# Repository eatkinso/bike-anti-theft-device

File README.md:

# Bike Anti-Theft Device

A portable, concealed device to prevent bike theft and facilitate tracking, centered around the STM32WLCC integrated microcontroller and SubGHz transceiver. This project was created for [ECE445 Spring 2022 at the University of Illinois at Urbana-Champaign](https://courses.physics.illinois.edu/ece445/projects.asp). 

# Development Folder Structure

- *Documentation*: Proposal, design document, final paper, and presentation for ECE 445. 
- *References*: Selected datasheets and reference manuals. 
- *Notebooks*: Lab notebooks during the development process. 
- *Hardware*: KiCAD schematic and layout files for each board used in the project. 
- *Firmware*: Microcontroller code for the STM32WLCC used in our project. Note that the final demo code is in SingleCore_UART -- the other folders contain various debugging firmware projects since it is easier to keep track of things during the development process by re-initializing a project in CubeMX for different tests rather than continuously using the same project. 

# Lab Notebook Structure

- Each group member will write entries in their markdown notebook to describe the development and debugging process. 
- Daily notebook entries must have a descriptive title, date, and the user's name. 
- Notebook entries referring to specific features, etc should identify the feature by its commit hash. For readability it may be better to embed images (of schematics, test setups, hand sketches etc) in the markdown notebook itself depending on the context.
- Lab notebook entries will not be removed or modified once written down. 
- Lab data, code to generate plots, etc is in a different folder since it is shared. Always save the original data for all trials, even if you only end up using some of the data for the analysis. 

# Workflow notes 
- VScode is convenient to write and render markdown. 
- TEXstudio is convenient to write and render LaTEX documents for reports, etc. Always save the .tex source to git, not the generated PDF. 
- Always commit the ENTIRE kicad project directory for PCBs. This prevents issues with footprint and symbol libraries 
since the entire project directory includes the backup and symbol rescue files.
- STM32CubeMX is used to generate peripheral initialization code and makefiles. We used an STLINK-V3 with [Black Magic Probe](https://github.com/blackmagic-debug/blackmagic) firmware running in PC-hosted mode for debugging.

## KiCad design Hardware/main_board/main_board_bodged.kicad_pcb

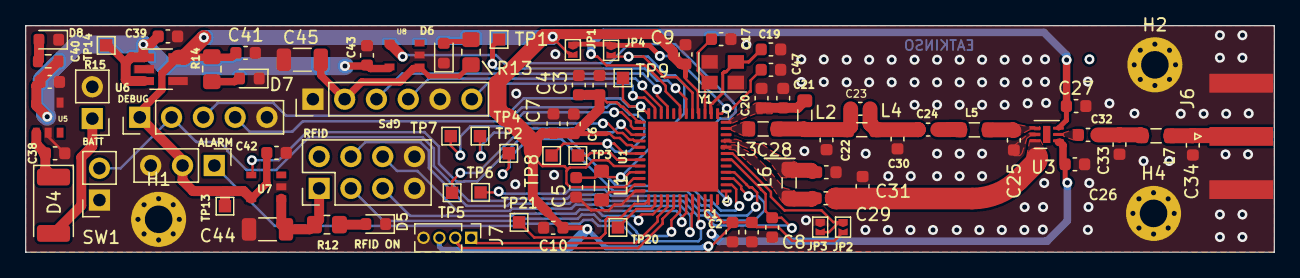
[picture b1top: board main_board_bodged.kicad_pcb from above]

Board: 2 copper layers, 99.8 x 18.1 mm, 87 parts (0 on the bottom side), 55 nets.

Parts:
C1, C3, C9, C10: 4.7u; C_0603_1608Metric
C2, C4: 100n; C_0603_1608Metric
C5: 470n; C_0603_1608Metric
C6, C38, C39, C40, C41, C42, C43, C47: 1u; C_0603_1608Metric
C7: 10n; C_0603_1608Metric
C8: 0.1u; C_0603_1608Metric
C17, C19: 22p; C_0603_1608Metric
C20: 47n; C_0603_1608Metric
C21, C24: 68p; C_0603_1608Metric
C22: 0.7p; C_0603_1608Metric
C23: 2p; C_0603_1608Metric
C25: DNP; C_0603_1608Metric
C26, C27: 1000p; C_0603_1608Metric
C28: 4.7p; C_0603_1608Metric
C29: 3p; C_0603_1608Metric
C30: 5.1p; C_0603_1608Metric
C31: 1p; C_0603_1608Metric
C32: 56p; C_0603_1608Metric
C33, C34: 3.3p; C_0603_1608Metric
C44, C45: 10u; C_1206_3216Metric
D4: D; D_2010_5025Metric
D5, D6, D7, D8: LED; LED_0603_1608Metric
H1, H2, H4: MountingHole_Pad; MountingHole_2.2mm_M2_Pad_Via
J1: ALARM; PinHeader_1x03_P2.54mm_Vertical
J2: RFID_CONN; PinHeader_2x04_P2.54mm_Vertical
J3: GPS_CONN; PinHeader_1x06_P2.54mm_Vertical
J5: DEBUG; PinHeader_1x05_P2.54mm_Vertical
J6: ANTENNA2; SMA_Amphenol_132289_EdgeMount
J7: Conn_01x04_Male; PinHeader_1x04_P1.27mm_Vertical
J8: BATT; PinHeader_1x02_P2.54mm_Vertical
JP1: SolderJumper_2_Bridged; tinyjumper
JP2, JP3, JP4: SolderJumper_2_Open; tinyjumper
L1: 15u; L_0805_2012Metric_Pad1.05x1.20mm_HandSolder
L2: 47n; L_0805_2012Metric_Pad1.05x1.20mm_HandSolder
L3: 4.45n; L_0805_2012Metric_Pad1.05x1.20mm_HandSolder
L4: 3.6n; L_0805_2012Metric_Pad1.05x1.20mm_HandSolder
L5: 8.7n; L_0805_2012Metric_Pad1.05x1.20mm_HandSolder
L6: 11n; L_0805_2012Metric_Pad1.05x1.20mm_HandSolder
L7: 9.1n; L_0805_2012Metric_Pad1.05x1.20mm_HandSolder
R12, R13, R14: 200R; R_0805_2012Metric_Pad1.20x1.40mm_HandSolder
R15: 200R; R_0603_1608Metric
SW1: SW_Push; PinSocket_1x02_P2.54mm_Vertical
TP1, TP2, TP3, TP4, TP5, TP6, TP7, TP8, TP9, TP13, TP14, TP20, TP21: TestPoint; TestPoint_Pad_1.0x1.0mm
U1: STM32WL55_UFQFPN48; QFN-48-1EP_7x7mm_P0.5mm_EP5.6x5.6mm
U3: SKY13370-374LF; DFN-6-1EP_2x2mm_P0.5mm_EP0.6x1.37mm
U5: AP7370-50W5-7; SOT25
U6: S-1135A33-M5T1U; SOT-23-5_HandSoldering
U7, U8: AP22811BW5-7; SOT25
Y1: Crystal_GND24; Oscillator_SMD_Abracon_ASE-4Pin_3.2x2.5mm

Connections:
+3V3: C1.1, C2.1, C3.1, C4.1, C6.1, C7.1, C9.1, C10.1, C41.1, C42.1, J1.2, J5.1, J7.3, JP1.2 (B), JP2.2 (B), R14.1, TP13.1, U1.11 (VDD), U1.28 (VDDRF), U1.37 (VBAT), U1.41 (VDDA), U1.44 (VDD), U1.46 (VDDSMPS), U6.5 (VOUT), U7.5 (IN)
+3V3_RFID: C44.1, J2.1, R12.1, U7.1 (OUT)
+5V: C39.1, C40.1, C43.1, R15.2, TP14.1, U5.5 (VOUT), U6.1 (VIN), U6.3 (ON), U8.5 (IN)
+5V_GPS: C45.1, J3.2, R13.1, U8.1 (OUT)
DBUG_JTDO_SWO: TP21.1, U1.1 (PB3)
DEBUG_JTCK_SWCLK: J5.4, TP8.1, U1.42 (PA14)
DEBUG_JTDI: TP3.1, U1.43 (PA15)
DEBUG_JTMS_SWDIO: J5.3, TP9.1, U1.36 (PA13)
DEBUG_JTRST: TP20.1, U1.2 (PB4)
GND: C1.2, C2.2, C3.2, C4.2, C5.2, C6.2, C7.2, C8.2, C9.2, C10.2, C17.1, C19.1, C20.2, C21.2, C22.2, C25.2, C26.1, C27.2, C28.2, C30.2, C31.1, C33.2, C34.2, C38.2, C39.2, C40.2, C41.2, C42.2, C43.2, C44.2, C45.2, C47.2, D5.1 (K), D6.1 (K), D7.1 (K), D8.1 (K), H1.1, H2.1, H4.1, J1.3, J2.7, J2.8, J3.1, J3.5, J5.5, J6.2 (Ext), J7.4, J8.2, JP3.1 (A), SW1.1, U1.48 (VSSSMPS), U3.5 (GND), U5.2 (GND), U5.4 (NC), U6.2 (VSS), U6.4 (NC), U7.2 (GND), U8.2 (GND), Y1.2, Y1.4
GPS_~PWR: U1.13 (PA5), U8.4 (~EN)
LPUART1_NRX: C26.2, U1.10 (PA3), U3.1 (VC1)
LPUART1_NTX: J1.1, U1.9 (PA2)
NRST: C8.1, J5.2, SW1.2, U1.18 (NRST)
unnamed: C5.1, JP4.2 (B), L1.1, U1.29 (VDDRF1V55), U1.45 (VFBSMPS)
unnamed: C17.2, U1.27 (OSC_OUT), Y1.1
unnamed: C19.2, U1.26 (OSC_IN), Y1.3
unnamed: C20.1, C21.1, L2.1, U1.24 (VR_PA)
unnamed: C22.1, C23.1, L2.2, L3.2, L4.1
unnamed: C23.2, C24.1, C30.1, L4.2
unnamed: C24.2, L5.1
unnamed: C25.1, L5.2, U3.4 (RF2)
unnamed: C28.1, L6.1, U1.21 (RFI_N)
unnamed: C29.1, L6.2, U1.20 (RFI_P)
unnamed: C29.2, C31.2, U3.6 (RF1)
unnamed: C32.1, U3.2 (RFC)
unnamed: C32.2, C33.1, L7.1
unnamed: C34.1, J6.1 (In), L7.2
unnamed: C38.1, D4.1 (K), U5.1 (VIN)
unnamed: C47.1, JP1.1 (A), JP4.1 (A), U1.25 (VDDPA)
unnamed: D4.2 (A), J8.1
unnamed: D5.2 (A), R12.2
unnamed: D6.2 (A), R13.2
unnamed: D7.2 (A), R14.2
unnamed: D8.2 (A), R15.1
unnamed: JP2.1 (A), JP3.2 (B), U1.19 (PH3-BOOT0)
unnamed: L1.2, U1.47 (VLXSMPS)
unnamed: L3.1, U1.23 (RFO_HP)
unnamed: TP1.1, U1.30 (PB0-VDD_TXCO)
unnamed: TP2.1, U1.16 (PA8)
unnamed: TP4.1, U1.40 (PC15-OSC32_OUT)
unnamed: TP5.1, U1.39 (PC14-OSC32_IN)
unnamed: TP6.1, U1.15 (PA7)
unnamed: TP7.1, U1.38 (PC13)
PA0: J2.6, U1.7 (PA0)
PA1: J2.4, U1.8 (PA1)
PA11: J3.4, U1.34 (PA11)
PA12: J3.6, U1.35 (PA12)
PB5: J2.5, U1.3 (PB5)
PB7: J7.2, U1.5 (PB7)
PB8: J2.3, U1.6 (PB8)
RFID_~PWR: U1.14 (PA6), U7.4 (~EN)
RFSW_VC2: C27.1, U1.31 (PB2), U3.3 (VC2)
USART1_RX: J3.3, U1.33 (PA10)
USART1_TX: J7.1, U1.4 (PB6)

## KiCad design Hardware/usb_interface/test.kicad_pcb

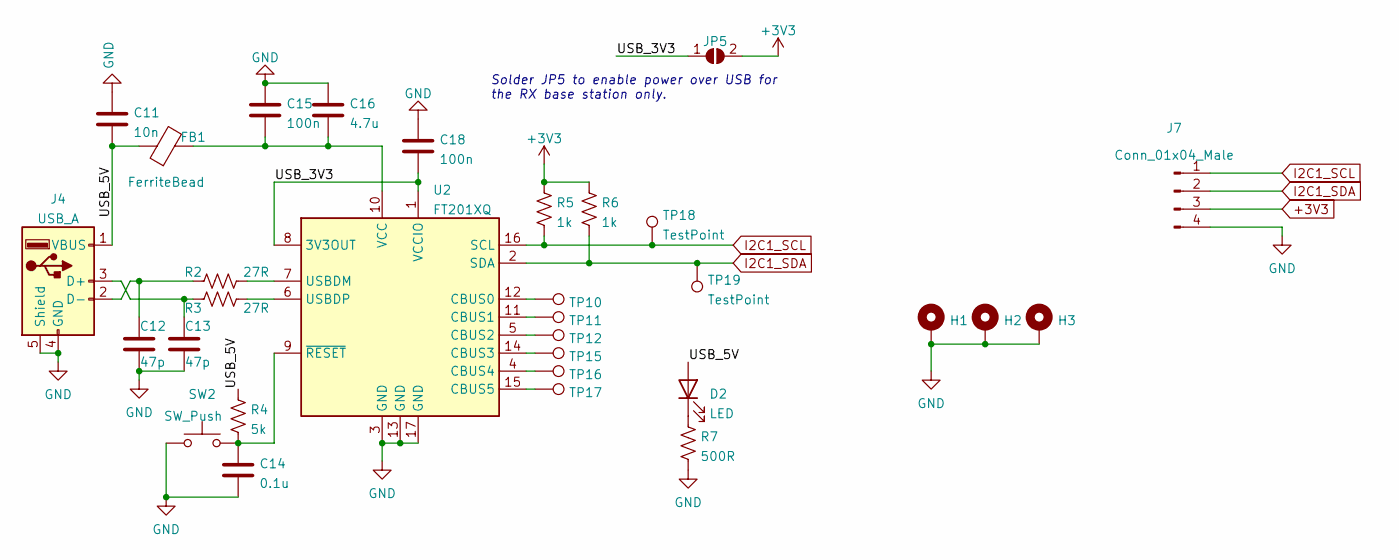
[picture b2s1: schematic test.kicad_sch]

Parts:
C11: 10n; C_0603_1608Metric
C12, C13: 47p; C_0603_1608Metric
C14: 0.1u; C_0603_1608Metric
C15, C18: 100n; C_0603_1608Metric
C16: 4.7u; C_0603_1608Metric
D2: LED; LED_0805_2012Metric
FB1: FerriteBead; LED_0805_2012Metric
H1, H2, H3: MountingHole_Pad; MountingHole_2.2mm_M2_Pad_Via
J4: USB_A; USB_A_Molex_67643_Horizontal
J7: Conn_01x04_Male; PinHeader_1x04_P1.27mm_Vertical
JP5: SolderJumper_2_Open; SolderJumper-2_P1.3mm_Open_RoundedPad1.0x1.5mm
R2, R3: 27R; R_0805_2012Metric_Pad1.20x1.40mm_HandSolder
R4: 5k; R_0805_2012Metric_Pad1.20x1.40mm_HandSolder
R5, R6: 1k; R_0805_2012Metric_Pad1.20x1.40mm_HandSolder
R7: 500R; R_0805_2012Metric_Pad1.20x1.40mm_HandSolder
SW2: SW_Push; PinSocket_1x02_P2.54mm_Vertical
TP10, TP11, TP12, TP15, TP16, TP17, TP18, TP19: TestPoint; TestPoint_Pad_1.0x1.0mm
U2: FT201XQ; QFN-16-1EP_4x4mm_P0.65mm_EP2.1x2.1mm

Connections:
+3V3: J7.3, JP5.2 (B), R5.1, R6.1
/USB_3V3: C18.2, JP5.1 (A), U2.1 (VCCIO), U2.8 (3V3OUT)
/USB_5V: C11.2, D2.2 (A), FB1.1, J4.1 (VBUS), R4.1
GND: C11.1, C12.2, C13.2, C14.2, C15.1, C16.1, C18.1, H1.1, H2.1, H3.1, J4.4 (GND), J4.5 (Shield), J7.4, R7.2, SW2.1, U2.3 (GND), U2.13 (GND), U2.17 (GND)
I2C1_SCL: J7.1, R5.2, TP18.1, U2.16 (SCL)
I2C1_SDA: J7.2, R6.2, TP19.1, U2.2 (SDA)
unnamed: C15.2, C16.2, FB1.2, U2.10 (VCC)
unnamed: C12.1, J4.2 (D-), R2.1
unnamed: C13.1, J4.3 (D+), R3.1
unnamed: D2.1 (K), R7.1
unnamed: TP16.1, U2.4 (CBUS4)
unnamed: TP12.1, U2.5 (CBUS2)
unnamed: R3.2, U2.6 (USBDP)
unnamed: R2.2, U2.7 (USBDM)
unnamed: C14.1, R4.2, SW2.2, U2.9 (~RESET)
unnamed: TP11.1, U2.11 (CBUS1)
unnamed: TP10.1, U2.12 (CBUS0)
unnamed: TP15.1, U2.14 (CBUS3)
unnamed: TP17.1, U2.15 (CBUS5)

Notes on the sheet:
Solder JP5 to enable power over USB for the RX base station only.

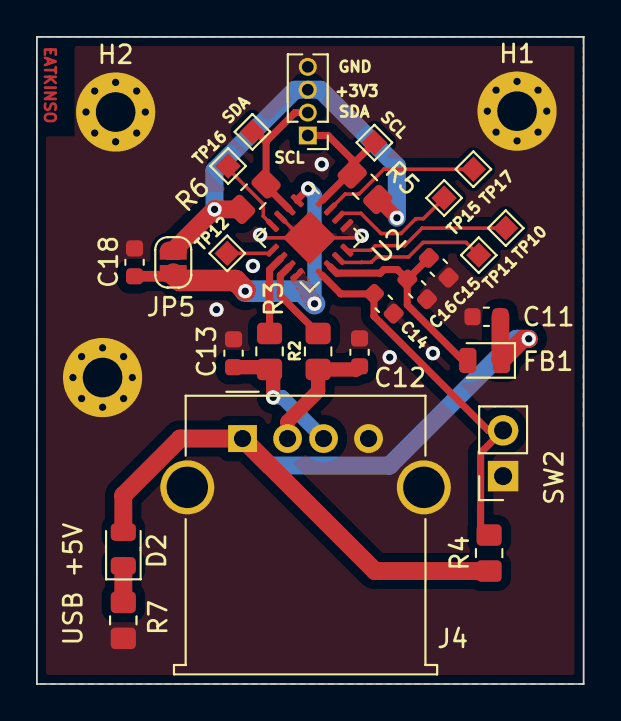
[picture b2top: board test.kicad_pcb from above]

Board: 2 copper layers, 30.4 x 35.9 mm, 31 parts (0 on the bottom side), 19 nets.

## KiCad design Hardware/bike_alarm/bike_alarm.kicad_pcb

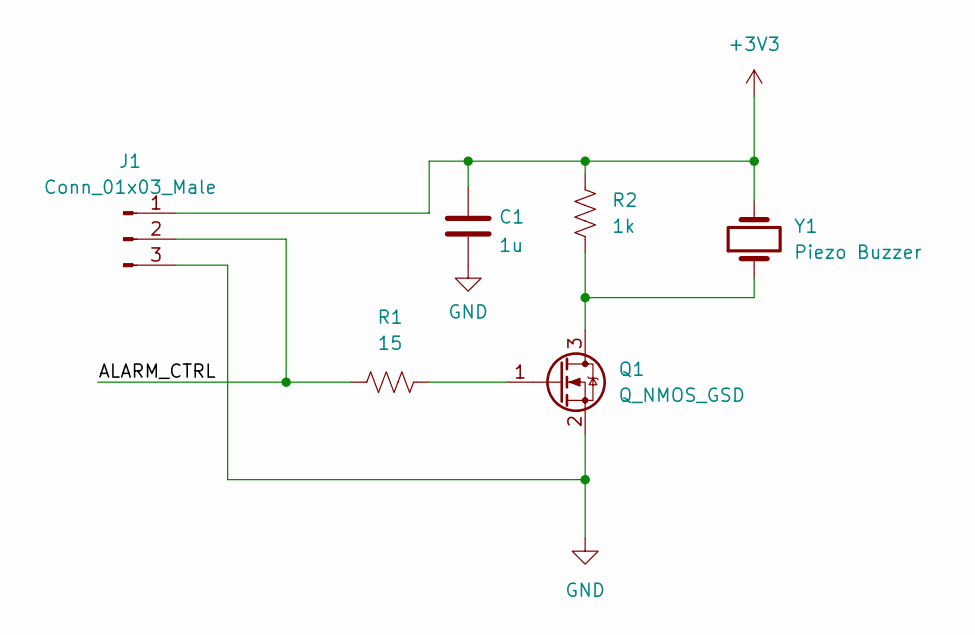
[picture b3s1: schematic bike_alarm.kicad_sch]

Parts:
C1: 1u; C_0805_2012Metric
J1: Conn_01x03_Male; PinHeader_1x03_P2.54mm_Vertical
Q1: Q_NMOS_GSD; SOT-23
R1: 15; R_0805_2012Metric_Pad1.20x1.40mm_HandSolder
R2: 1k; R_0805_2012Metric_Pad1.20x1.40mm_HandSolder
Y1: Piezo Buzzer; Crystal_AT310_D3.0mm_L10.0mm_Horizontal

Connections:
+3V3: C1.1, J1.1, R2.1, Y1.2
/ALARM_CTRL: J1.2, R1.1
GND: C1.2, J1.3, Q1.2 (S)
unnamed: Q1.1 (G), R1.2
unnamed: Q1.3 (D), R2.2, Y1.1

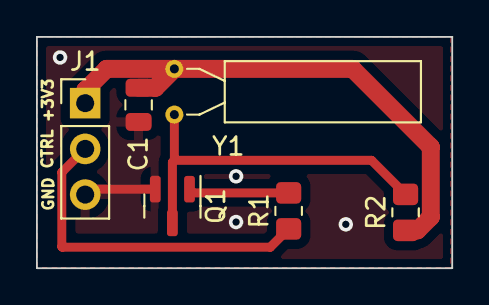
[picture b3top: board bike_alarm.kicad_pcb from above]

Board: 2 copper layers, 23.1 x 12.9 mm, 6 parts (0 on the bottom side), 5 nets.

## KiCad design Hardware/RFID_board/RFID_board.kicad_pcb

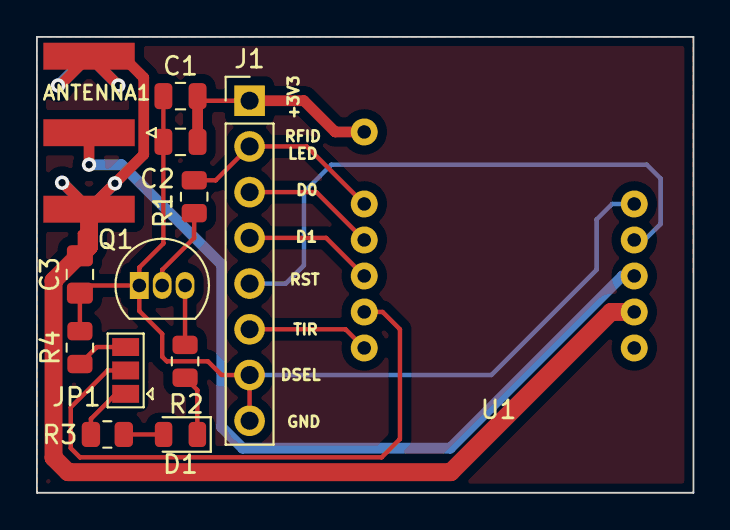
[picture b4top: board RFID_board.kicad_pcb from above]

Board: 2 copper layers, 36.5 x 25.3 mm, 13 parts (0 on the bottom side), 16 nets.

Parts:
ANTENNA1: 1.337m; SMA_Amphenol_132289_EdgeMount
C1: 10n; C_0805_2012Metric
C2: 1u; C_0805_2012Metric
C3: DNP; C_0805_2012Metric_Pad1.18x1.45mm_HandSolder
D1: LED; D_0805_2012Metric
J1: Conn_01x08_Male; PinHeader_1x08_P2.54mm_Vertical
JP1: SolderJumper_3_Open; SolderJumper-3_P1.3mm_Open_Pad1.0x1.5mm
Q1: 2N3904; TO-92_Inline
R1: 15R; R_0805_2012Metric
R2: 300R; R_0805_2012Metric
R3, R4: 1k; R_0805_2012Metric
U1: ID-3LA

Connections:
+3V3: D1.2 (A), R3.1
+3V3_RFID: C1.2, C2.2, J1.1, U1.11 (VCC)
GND: C1.1, C2.1, C3.1, J1.7, J1.8, Q1.1 (E), R4.2, U1.1 (GND)
unnamed: ANTENNA1.1, U1.3 (ANT)
unnamed: ANTENNA1.2, C3.2, U1.4 (ANT)
unnamed: D1.1 (K), R2.1
unnamed: J1.3, U1.9 (DATA0)
unnamed: J1.4, U1.8 (DATA1)
unnamed: J1.5, U1.2 (RST)
unnamed: J1.6, U1.6 (TAG_IN_RANGE)
unnamed: JP1.1 (A), R3.2
unnamed: JP1.2 (C), U1.7 (DATA_SELECT)
unnamed: JP1.3 (B), R4.1
unnamed: Q1.2 (B), R1.2
unnamed: Q1.3 (C), R2.2
RFID_LED: J1.2, R1.1, U1.10 (LED)

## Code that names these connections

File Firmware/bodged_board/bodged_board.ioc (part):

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Mcu.Name=STM32WL55CCUx
Mcu.Package=UFQFPN48
Mcu.UserName=STM32WL55CCUx
PA0.GPIOParameters=GPIO_Label
PA0.GPIO_Label=RFID_TAG_IN_RANGE
PA0.Signal=GPIO_Input
PA1.GPIOParameters=GPIO_Label
PA1.GPIO_Label=RFID_DATA1
PA1.Signal=GPIO_Input
PA10.Mode=Asynchronous
PA10.Signal=USART1_RX
PA11.GPIOParameters=GPIO_Label
PA11.GPIO_Label=RFID_STATE
PA11.Signal=GPIO_Input
PA13.Mode=JTAG_5_pins
PA13.Signal=DEBUG_JTMS-SWDIO
PA14.Mode=JTAG_5_pins
PA14.Signal=DEBUG_JTCK-SWCLK
PA15.Mode=JTAG_5_pins
PA15.Signal=DEBUG_JTDI
PA2.GPIOParameters=GPIO_Label
PA2.GPIO_Label=ALARM_ON
PA2.Signal=GPIO_Output
PA3.GPIOParameters=GPIO_Label
PA3.GPIO_Label=RFSW_VC1
PA3.Signal=GPIO_Output
PA5.GPIOParameters=GPIO_Label
PA5.GPIO_Label=GPS_NPWR
PA5.Signal=GPIO_Output
PA6.GPIOParameters=GPIO_Label
PA6.GPIO_Label=RFID_NPWR
PA6.Signal=GPIO_Output
PB12.GPIOParameters=GPIO_Label
PB12.GPIO_Label=RFID_DATA0
PB12.Signal=GPIO_Output
PB2.GPIOParameters=GPIO_Label
PB2.GPIO_Label=RFSW_VC2
PB2.Signal=GPIO_Output
PB3.Mode=JTAG_5_pins
PB3.Signal=DEBUG_JTDO-SWO
PB4.Mode=JTAG_5_pins
PB4.Signal=DEBUG_JTRST
PB5.GPIOParameters=GPIO_Label
PB5.GPIO_Label=RFID_NRST
PB5.Signal=GPIO_Output
PB6.Mode=Asynchronous
PB6.Signal=USART1_TX
PB7.Mode=I2C
PB7.Signal=I2C1_SDA
PB8.Mode=I2C
PB8.Signal=I2C1_SCL
RCC.HSE_VALUE=26000000
RCC.SYSCLKFreq_VALUE=32000000
board=custom

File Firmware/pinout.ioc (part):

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Mcu.Name=STM32WL55CCUx
Mcu.Package=UFQFPN48
Mcu.UserName=STM32WL55CCUx
PA0.GPIOParameters=GPIO_Label
PA0.GPIO_Label=RFID_TAG_IN_RANGE
PA0.Signal=GPIO_Input
PA1.GPIOParameters=GPIO_Label
PA1.GPIO_Label=RFID_DATA1
PA1.Signal=GPIO_Input
PA10.GPIOParameters=GPIO_Label
PA10.GPIO_Label=GPS_RXD
PA10.Signal=GPIO_Output
PA11.GPIOParameters=GPIO_Label
PA11.GPIO_Label=GPS_STATE
PA11.Signal=GPIO_Input
PA12.GPIOParameters=GPIO_Label
PA12.GPIO_Label=GPS_TXD
PA12.Signal=GPIO_Input
PA13.Mode=JTAG_5_pins
PA13.Signal=DEBUG_JTMS-SWDIO
PA14.Mode=JTAG_5_pins
PA14.Signal=DEBUG_JTCK-SWCLK
PA15.Mode=JTAG_5_pins
PA15.Signal=DEBUG_JTDI
PA2.GPIOParameters=GPIO_Label
PA2.GPIO_Label=ALARM_ON
PA2.Signal=GPIO_Output
PA3.GPIOParameters=GPIO_Label
PA3.GPIO_Label=RFSW_VC1
PA3.Signal=GPIO_Output
PA4.Mode=SUBGHZSPI-Monitoring
PA4.Signal=DEBUG_SUBGHZSPI-NSSOUT
PA5.Mode=SUBGHZSPI-Monitoring
PA5.Signal=DEBUG_SUBGHZSPI-SCKOUT
PA6.Mode=SUBGHZSPI-Monitoring
PA6.Signal=DEBUG_SUBGHZSPI-MISOOUT
PA7.Mode=SUBGHZSPI-Monitoring
PA7.Signal=DEBUG_SUBGHZSPI-MOSIOUT
PB3.Mode=JTAG_5_pins
PB3.Signal=DEBUG_JTDO-SWO
PB4.Mode=JTAG_5_pins
PB4.Signal=DEBUG_JTRST
PB5.GPIOParameters=GPIO_Label
PB5.GPIO_Label=RFID_NRST
PB5.Signal=GPIO_Output
PB6.Mode=I2C
PB6.Signal=I2C1_SCL
PB7.Mode=I2C
PB7.Signal=I2C1_SDA
PB8.GPIOParameters=GPIO_Label
PB8.GPIO_Label=RFID_DATA0
PB8.Signal=GPIO_Input
PC14-OSC32_IN.Mode=LSE-External-Oscillator
PC14-OSC32_IN.Signal=RCC_OSC32_IN
PC15-OSC32_OUT.Mode=LSE-External-Oscillator
PC15-OSC32_OUT.Signal=RCC_OSC32_OUT
RCC.HSE_VALUE=26000000
RCC.SYSCLKFreq_VALUE=32000000
board=custom

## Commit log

2022-02-08 proposal work
2022-02-08 added requirements
2022-02-08 more block diagram and notebook entry
2022-02-09 finished block diagram
2022-02-17 latest notebook entry
2022-02-20 main board work, docs, stm32cubemx files
2022-02-21 more main pcb work (changed pinout, added USB interface), additional reference docs
2022-02-22 add bike alarm
2022-02-22 example ckt stuff
2022-03-04 split schematic into separate board
2022-03-06 bike_alarm pcb update and bom
2022-03-06 update bom
2022-03-06 finished rfid pcb
2022-03-07 finished main board
2022-03-07 all boards pass DRC and have appropriate silkscreens, will order tomorrow
2022-03-08 usb interface
2022-04-02 daily notes EA
2022-04-07 ughh
2022-04-11 I HATE IT HERE
2022-04-12 safety commit
2022-04-12 mostly notes
2022-04-12 stuff
2022-04-13 more notes etc
2022-04-14 lora helper functions
2022-04-14 sussy static functions
2022-04-19 safety commit, uart working kinda
2022-04-19 GPS parser v1
2022-04-22 dummy nucleo uart device for python gui backend development
2022-04-22 changed notebook structure
2022-04-22 RFID working over serial
2022-04-23 random work from yesterday and gps distance calculation stuff
2022-04-24 rip my radio... calling it a day for tn
2022-04-25 hahahhah
2022-04-25 finished for tn
2022-04-26 final firmware
2022-05-03 presentation
2022-05-04 moving to github from UIUC gitlab
2022-05-04 cleaned up file structure
2022-05-05 finish merge add files
2022-05-07 upload gui src code vs 1.0.0
2022-05-07 Delete gui.py
    not the most recent vs
